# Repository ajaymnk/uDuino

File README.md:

# uDuino
Arduino compatible AVR Development Board

#### Top Layer

#### Bottom Layer

#### 3D View
<a href="https://sketchfab.com/models/0a4b825f3d744794a45e6b6fafa52535">
</a>

---
#### Want to order the board

## License
[Creative Commons Attribution Share Alike 4.0](https://creativecommons.org/licenses/by-sa/4.0/)

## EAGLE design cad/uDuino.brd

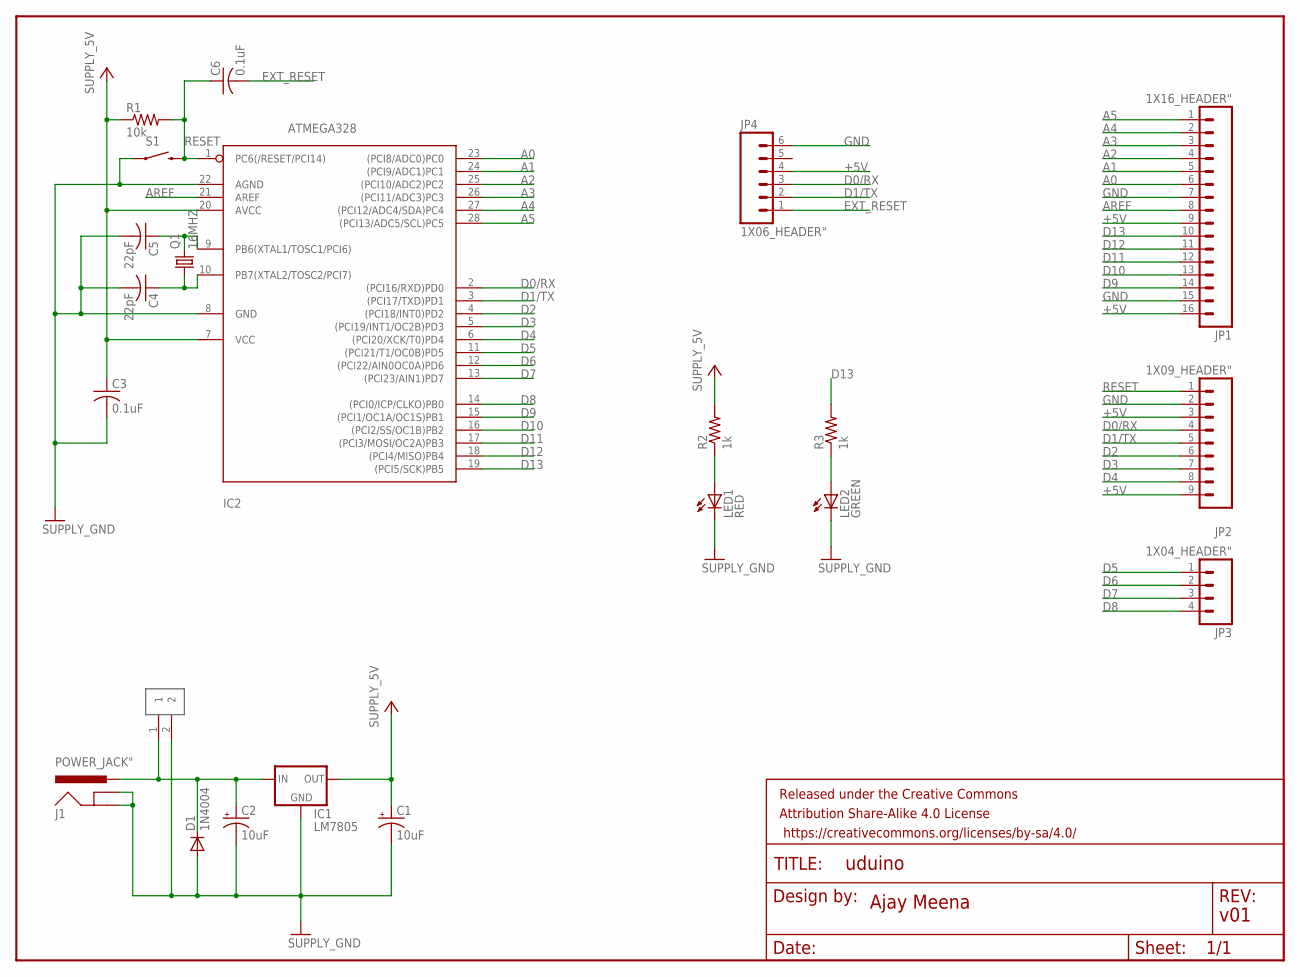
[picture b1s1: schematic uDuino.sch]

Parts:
C1, C2: 10uF; ELECTROLYTIC_CAP
C3, C6: 0.1uF; UNPOLARIZED_CAP
C4, C5: 22pF; UNPOLARIZED_CAP
D1: 1N4004; DO41-10
FRAME1: FRAME-LETTERNO_PACKAGE; DUMMY
IC1: LM7805; L4931_REGULATOR
IC2: ATMEGA328
J1: POWER_JACK"; POWER_JACK
JP1: 1X16_HEADER"; 1X16_HEADER
JP2: 1X09_HEADER"; 1X09_HEADER
JP3: 1X04_HEADER"; 1X04_HEADER
JP4: 1X06_HEADER"; 1X06_HEADER
JP5: 1X02_HEADER
LED1: RED; LED5MM
LED2: GREEN; LED5MM
Q1: 16MHZ; HC49/S
R1: 10k; 0204/7
R2, R3: 1k; 0204/7
S1: MOMENTARY_SWITCH"; MOMENTARY_SWITCH

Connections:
+5V: C1.+, C3.1, IC1.OUT, IC2.7 (VCC), IC2.20 (AVCC), JP1.9, JP1.16, JP2.3, JP2.9, JP4.4, R1.1, R2.2
A0: IC2.23 ((PCI8/ADC0)PC0), JP1.6
A1: IC2.24 ((PCI9/ADC1)PC1), JP1.5
A2: IC2.25 ((PCI10/ADC2)PC2), JP1.4
A3: IC2.26 ((PCI11/ADC3)PC3), JP1.3
A4: IC2.27 ((PCI12/ADC4/SDA)PC4), JP1.2
A5: IC2.28 ((PCI13/ADC5/SCL)PC5), JP1.1
AREF: IC2.21 (AREF), JP1.8
D0/RX: IC2.2 ((PCI16/RXD)PD0), JP2.4, JP4.3
D1/TX: IC2.3 ((PCI17/TXD)PD1), JP2.5, JP4.2
D2: IC2.4 ((PCI18/INT0)PD2), JP2.6
D3: IC2.5 ((PCI19/INT1/OC2B)PD3), JP2.7
D4: IC2.6 ((PCI20/XCK/T0)PD4), JP2.8
D5: IC2.11 ((PCI21/T1/OC0B)PD5), JP3.1
D6: IC2.12 ((PCI22/AIN0OC0A)PD6), JP3.2
D7: IC2.13 ((PCI23/AIN1)PD7), JP3.3
D8: IC2.14 ((PCI0/ICP/CLKO)PB0), JP3.4
D9: IC2.15 ((PCI1/OC1A/OC1S)PB1), JP1.14
D10: IC2.16 ((PCI2/SS/OC1B)PB2), JP1.13
D11: IC2.17 ((PCI3/MOSI/OC2A)PB3), JP1.12
D12: IC2.18 ((PCI4/MISO)PB4), JP1.11
D13: IC2.19 ((PCI5/SCK)PB5), JP1.10, R3.2
EXT_RESET: C6.2, JP4.1
GND: C1.-, C2.-, C3.2, C4.2, C5.2, D1.A, IC1.GND, IC2.8 (GND), IC2.22 (AGND), J1.GND, J1.GNDBREAK, JP1.7, JP1.15, JP2.2, JP4.6, JP5.2, LED1.K (C), LED2.K (C), S1.1
unnamed: C2.+, D1.C, IC1.IN, J1.PWR, JP5.1
unnamed: C5.1, IC2.9 (PB6(XTAL1/TOSC1/PCI6)), Q1.2
unnamed: C4.1, IC2.10 (PB7(XTAL2/TOSC2/PCI7)), Q1.1
unnamed: LED2.A, R3.1
unnamed: LED1.A, R2.1
RESET: C6.1, IC2.1 (PC6(/RESET/PCI14)), JP2.1, R1.2, S1.3 (2)

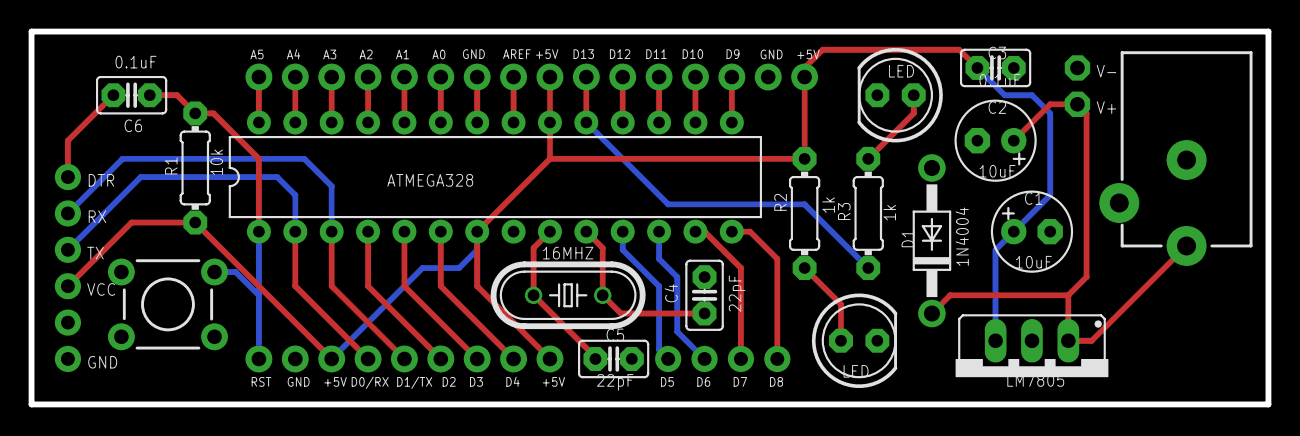
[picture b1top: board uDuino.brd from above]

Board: 2 copper layers, 86.4 x 26.0 mm, 23 parts (0 on the bottom side), 30 nets.

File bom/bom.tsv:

References	Qty	Description	Manufacturer	MPN	Digikey	Mouser	Newark	Farnell
S1	1	Pushbutton Switch	E-Switch	TL1105AF250Q	EG1830-ND	TL1105AF250Q	15N4466	1633012
IC1	1	LM7805 Voltage Regulator	Fairchild Semiconductor	LM7805ACT	LM7805ACT-ND	LM7805ACT	87X8928	2296047
Q1	1	16mhz Crystal	Fox Electronics	FOXSLF/160-20	631-1108-ND	FOXSLF/160-20	58T1826	2057965
IC2	1	ATMEGA328P	Microchip	ATMEGA328-PU	ATMEGA328-PU-ND	ATMEGA328-PU	68T2932	1972087
D1	1	1N4004 Diode	ON Semiconductor	1N4004G	1N4004GOS-ND	1N4004G	42K2822	1651084
"C1, C2"	2	10 uf Electrolytic Capacitor	Panasonic	ECE-A1VKS100	P980-ND	ECE-A1VKS100	55T0262	1902010
"R2, R3"	2	1k Resistor	Panasonic	ERG-1SJ102	P1.0KW-1BK-ND	ERG-1SJ102	52W6823	2324488
J1	1	DC Power Jack	Switchcraft	RAPC712BK	SC1863-ND	RAPC712BK	03M4244	2579769
"JP1, JP2, JP3, JP4, JP5"	1	Single row Male headers	TE Connectivity	5-826947-0	A105203-ND	5-826947-0	08N2872	1580058
"C4, C5"	2	22pf Ceramic Capacitor	Vishay BCcomponents	S220K25SL0N63L6R	1270PH-ND	S220K25SL0N63L6R	92K9515	1606192
"C3, C6"	2	0.1 uf Ceramic Capacitor	Vishay	K104K10X7RF5UH5	BC2665CT-ND	K104K10X7RF5UH5	75Y1233	2507749
R1	1	10k Resistor	Vishay	MRS25000C1002FCT00	BC3326CT-ND	MRS25000C1002FCT00	72K6539	9463976
"LED1, LED2"	2	LED 5MM	Vishay	TLUV5300	TLUV5300-ND	TLUV5300	33C1443	1045375

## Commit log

2017-02-22 Added LED at D13
2017-03-12 renamed uDuino.pdf to uDuino-silkscreen.pdf
2017-03-12 Update DESCRIPTION
2017-03-12 Added LICENSE
2017-04-03 Adding 3d view
2017-06-28 changed frame
2017-06-29 Added gerber files
2017-06-29 leading zero suppression
2017-06-30 Adding project to kitnic.it
2017-06-30 Improve bom part selection a little
2017-06-30 Updated Newark and Farnell carts
    Added alternative parts for US and UK only stock
2017-09-06 updated 3d view
2019-06-13 Set theme jekyll-theme-cayman
2019-06-13 Set theme jekyll-theme-minimal
2019-06-13 Set theme jekyll-theme-hacker

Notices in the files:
parts and their libraries:
SparkFun-Aesthetics: Licensing: Creative Commons ShareAlike 4.0 International - https://creativecommons.org/licenses/by-sa/4.0
SparkFun-Aesthetics: Released under the Creative Commons Attribution Share-Alike 4.0 License
SparkFun-Aesthetics: Released under the Creative Commons
